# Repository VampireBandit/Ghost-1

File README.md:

## GHOST-1

A Drone made with a transceiver and flight controller that I made. There is nothing much to say about this because it speaks for itself. Well it's ment to  be fast. And one of the most fun thing about this is its fully diy. From the trasmitter to the flight controller.  The firmware for the flight controller is from opensource Betaflight github. 

## Controlling

This is the transmitter that's used. Checkout https://github.com/VampireBandit/Transceiver_101

## Cortex

The flight controller is called "Cortex". This is made using an esp32 and an MPU6050 module. This will allow the drone to be able to load Betaflight firmware in it. The betaflight firmware is taken from the git for the open source betaflight. 

## BOM
| Name | Purpose | Quantity | Total Cost | Link | Distributor |
| :--- | :--- | :--- | :--- | :--- | :--- |
| **M3 screws** | Holding the case | 8 | 3.44 | [Link](https://wv) | Aliexpress |
| **NRF module** | radio transmission | 1 | 5.42 | [Link](https://wv) | Aliexpress |
| **Esp32_cAM** | Camera | 1 | 12.82 | [Link](https://wv) | Aliexpress |
| **Arduino_nano** | Receiver node | 1 | 5 | [Link](https://wv) | Aliexpress |
| **ESC_mini** | Speed control | 4 | 19.18 | [Link](https://wv) | Aliexpress |
| **5" drone props** | Propulsion | 4 | 37.66 | [Link](https://wv) | Aliexpress |
| **6s 1400mah** | power | 1 | 19.13 | [Link](https://wv) | Aliexpress |
| **BLDC motor** | Motor | 4 | 76.46 | [Link](https://wv) | Aliexpress |
| **Esp32** | flight_control | 1 | 7.77 | [Link](https://ali) | Aliexpress |
| **pcb** | Flight control | 5 | 20 | [Link](https://jlc) | jlcpcb |
| **Frame** | The drone frame | 1 | 50 | [Link](https://jlc) | jlc3dp |
| **Male headers** | connection | 8 | 4.33 | [Link](https://wv) | Aliexpress |
| **Female Headers** | Mounting | 56 | 6.36 | [Link](https://wv) | Aliexpress |
| **100nf capacitor** | Voltage capping | 2 | 1.07 | [Link](https://wv) | Aliexpress |
| **10uf capacitor** | Voltage regulation | 2 | 0.93 | [Link](https://s.c) | Aliexpress |
| **100uf capacitor** | Voltage regulation | 1 | 2.06 | [Link](https://s.c) | Aliexpress |
| **Arduino Nano** | MCU | 1 | 8.7 | [Link](https://wv) | Aliexpress |
| **Antenna** | Receiver antenna | 1 | 4.75 | [Link](https://wv) | Aliexpress |
| **Receiver Module** | Radio transmission | 1 | 5.62 | [Link](https://wv) | Aliexpress |
| **LM1117T-3.3** | Voltage regulator | 1 | 13.44 | [Link](https://wv) | Aliexpress |
| **Grand Total** | | | **304.14** | | |
Made by Rubaiyat_Islam

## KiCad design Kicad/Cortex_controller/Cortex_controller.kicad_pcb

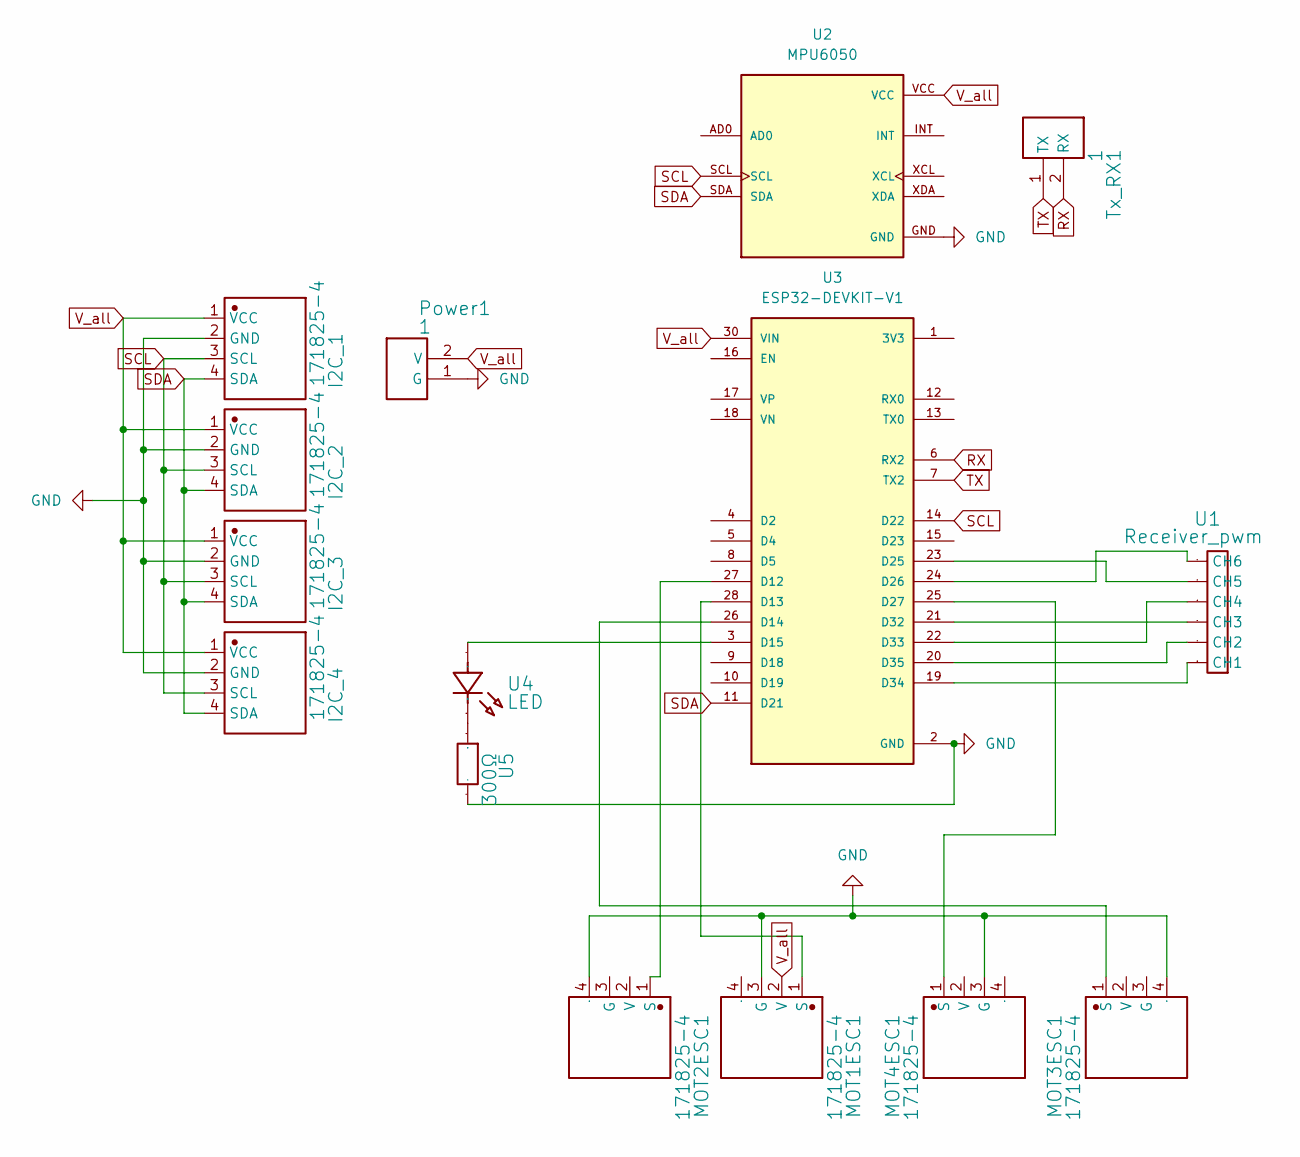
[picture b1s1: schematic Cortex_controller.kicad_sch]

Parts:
I2C_1, I2C_2, I2C_3, I2C_4: 171825-4; FanPinHeader_1x04_P2.54mm_Vertical; Manufacturer Part 171825-4
MOT1ESC1, MOT2ESC1, MOT3ESC1, MOT4ESC1: 171825-4; FanPinHeader_1x04_P2.54mm_Vertical; Manufacturer Part 171825-4
Power1: 1; PinHeader_1x02_P2.54mm_Vertical; Manufacturer Part Berg2
Tx_RX1: 1; PinHeader_1x02_P2.54mm_Vertical; Manufacturer Part Berg2
U1: Receiver_pwm; PinHeader_1x06_P2.54mm_Vertical
U2: MPU6050; MODULE_GY-521; PARTREV NA
U3: ESP32-DEVKIT-V1; MODULE_ESP32_DEVKIT_V1; PARTREV N/A
U4: LED; LED_D3.0mm; Manufacturer Part 15400394A3590
U5: 300Ω; R_Axial_DIN0207_L6.3mm_D2.5mm_P7.62mm_Horizontal; Manufacturer Part OF301JE

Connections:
GND: I2C_1.2 (GND), I2C_2.2 (GND), I2C_3.2 (GND), I2C_4.2 (GND), MOT1ESC1.3 (G), MOT2ESC1.4, MOT3ESC1.4, MOT4ESC1.3 (G), Power1.1 (G), U2.GND, U3.2 (GND), U3.29 (GND), U5.2
unnamed: MOT1ESC1.1 (S), U3.28 (D13)
unnamed: MOT2ESC1.1 (S), U3.27 (D12)
unnamed: MOT3ESC1.1 (S), U3.26 (D14)
unnamed: MOT4ESC1.1 (S), U3.25 (D27)
unnamed: U1.1 (CH1), U3.19 (D34)
unnamed: U1.2 (CH2), U3.20 (D35)
unnamed: U1.3 (CH3), U3.21 (D32)
unnamed: U1.4 (CH4), U3.22 (D33)
unnamed: U1.5 (CH5), U3.23 (D25)
unnamed: U1.6 (CH6), U3.24 (D26)
unnamed: U3.3 (D15), U4.2 (A)
unnamed: U4.1 (K), U5.1
RX: Tx_RX1.2 (RX), U3.6 (RX2)
SCL: I2C_1.3 (SCL), I2C_2.3 (SCL), I2C_3.3 (SCL), I2C_4.3 (SCL), U2.SCL, U3.14 (D22)
SDA: I2C_1.4 (SDA), I2C_2.4 (SDA), I2C_3.4 (SDA), I2C_4.4 (SDA), U2.SDA, U3.11 (D21)
TX: Tx_RX1.1 (TX), U3.7 (TX2)
V_all: I2C_1.1 (VCC), I2C_2.1 (VCC), I2C_3.1 (VCC), I2C_4.1 (VCC), MOT1ESC1.2 (V), Power1.2 (V), U2.VCC, U3.30 (VIN)

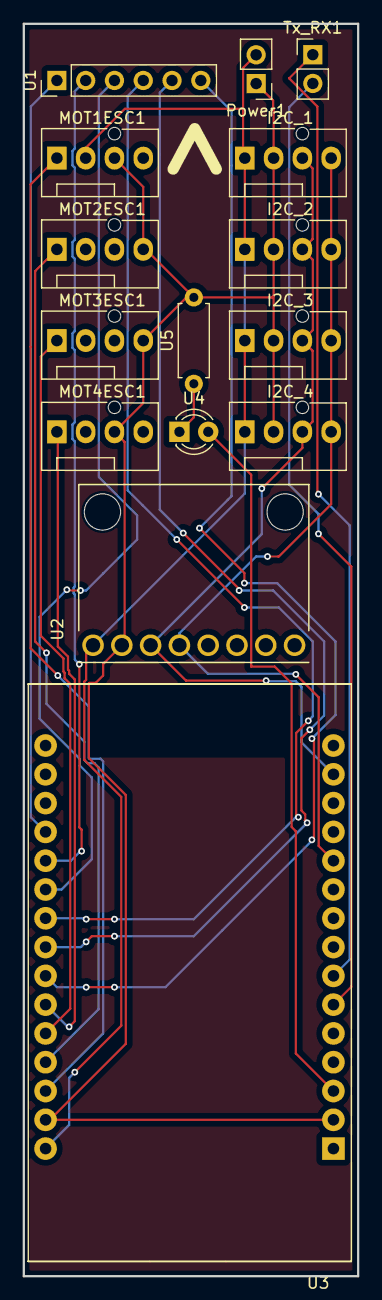
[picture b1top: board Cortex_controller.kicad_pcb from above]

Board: 2 copper layers, 29.5 x 110.5 mm, 15 parts (0 on the bottom side), 18 nets.

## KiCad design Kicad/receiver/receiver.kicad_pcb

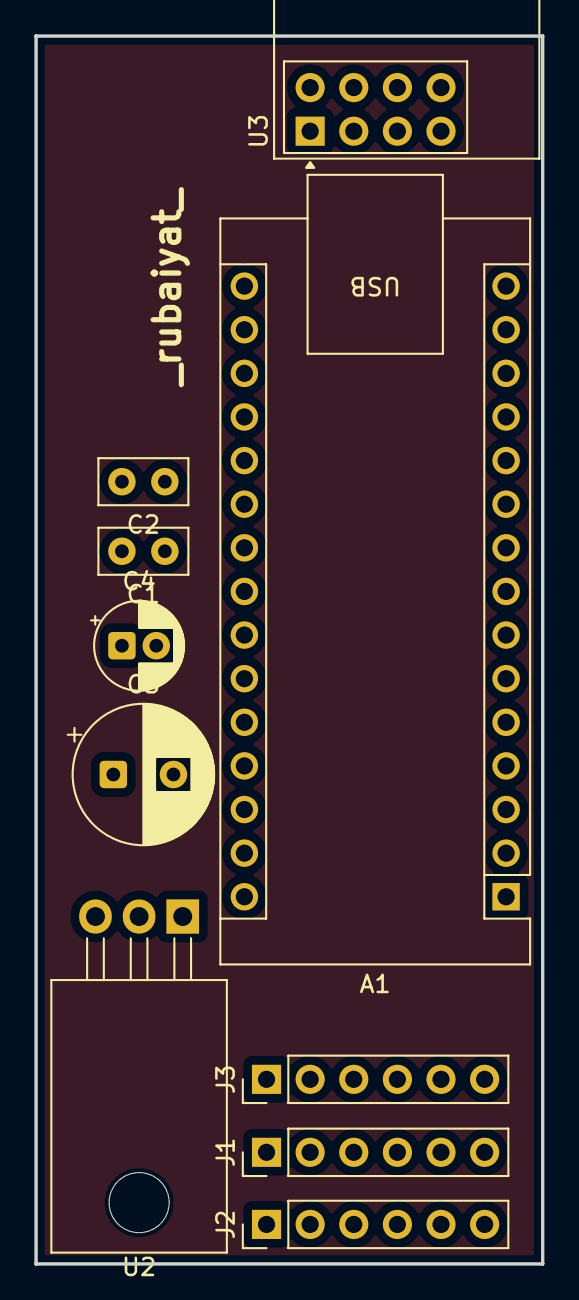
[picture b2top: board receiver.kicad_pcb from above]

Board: 2 copper layers, 29.5 x 71.5 mm, 10 parts (0 on the bottom side), 14 nets, no tracks yet.

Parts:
A1: Arduino_Nano_v3.x; Arduino_Nano
C1, C2: 100nf; C_Disc_D5.0mm_W2.5mm_P2.50mm
C3: 100μf; CP_Radial_D8.0mm_P3.50mm
C4: 10μf; CP_Radial_D5.0mm_P2.00mm
J1, J2, J3: Conn_01x06_Pin; PinHeader_1x06_P2.54mm_Vertical
U2: LM1117T-2.5; TO-220-3_Horizontal_TabDown
U3: NRF24L01_Breakout; nRF24L01_Breakout

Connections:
+3V3: A1.17 (3V3), C2.1, C3.1, U2.2 (VO), U3.2 (VCC)
CE: A1.12 (D9), U3.3 (CE)
CSN: A1.13 (D10), U3.4 (~CSN)
GND: A1.4 (GND), A1.29 (GND), C1.2, C2.2, C3.2, C4.2, J3.1, J3.2, J3.3, J3.4, J3.5, J3.6, U2.1 (GND), U3.1 (GND)
MISO: A1.15 (D12), U3.7 (MISO)
MOSI: A1.14 (D11), U3.6 (MOSI)
unnamed: A1.5 (D2), J2.1
unnamed: A1.6 (D3), J2.2
unnamed: A1.7 (D4), J2.3
unnamed: A1.8 (D5), J2.4
unnamed: A1.9 (D6), J2.5
unnamed: A1.10 (D7), J2.6
unnamed: A1.30 (VIN), C1.1, C4.1, J1.1, J1.2, J1.3, J1.4, J1.5, J1.6, U2.3 (VI)
SCK: A1.16 (D13), U3.5 (SCK)

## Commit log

2026-05-03 Fix grand total cost in BOM section
    Updated the grand total cost in the BOM section.
